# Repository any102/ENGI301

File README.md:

# ENGI301 <h>
Repository for ENGI 301 course work

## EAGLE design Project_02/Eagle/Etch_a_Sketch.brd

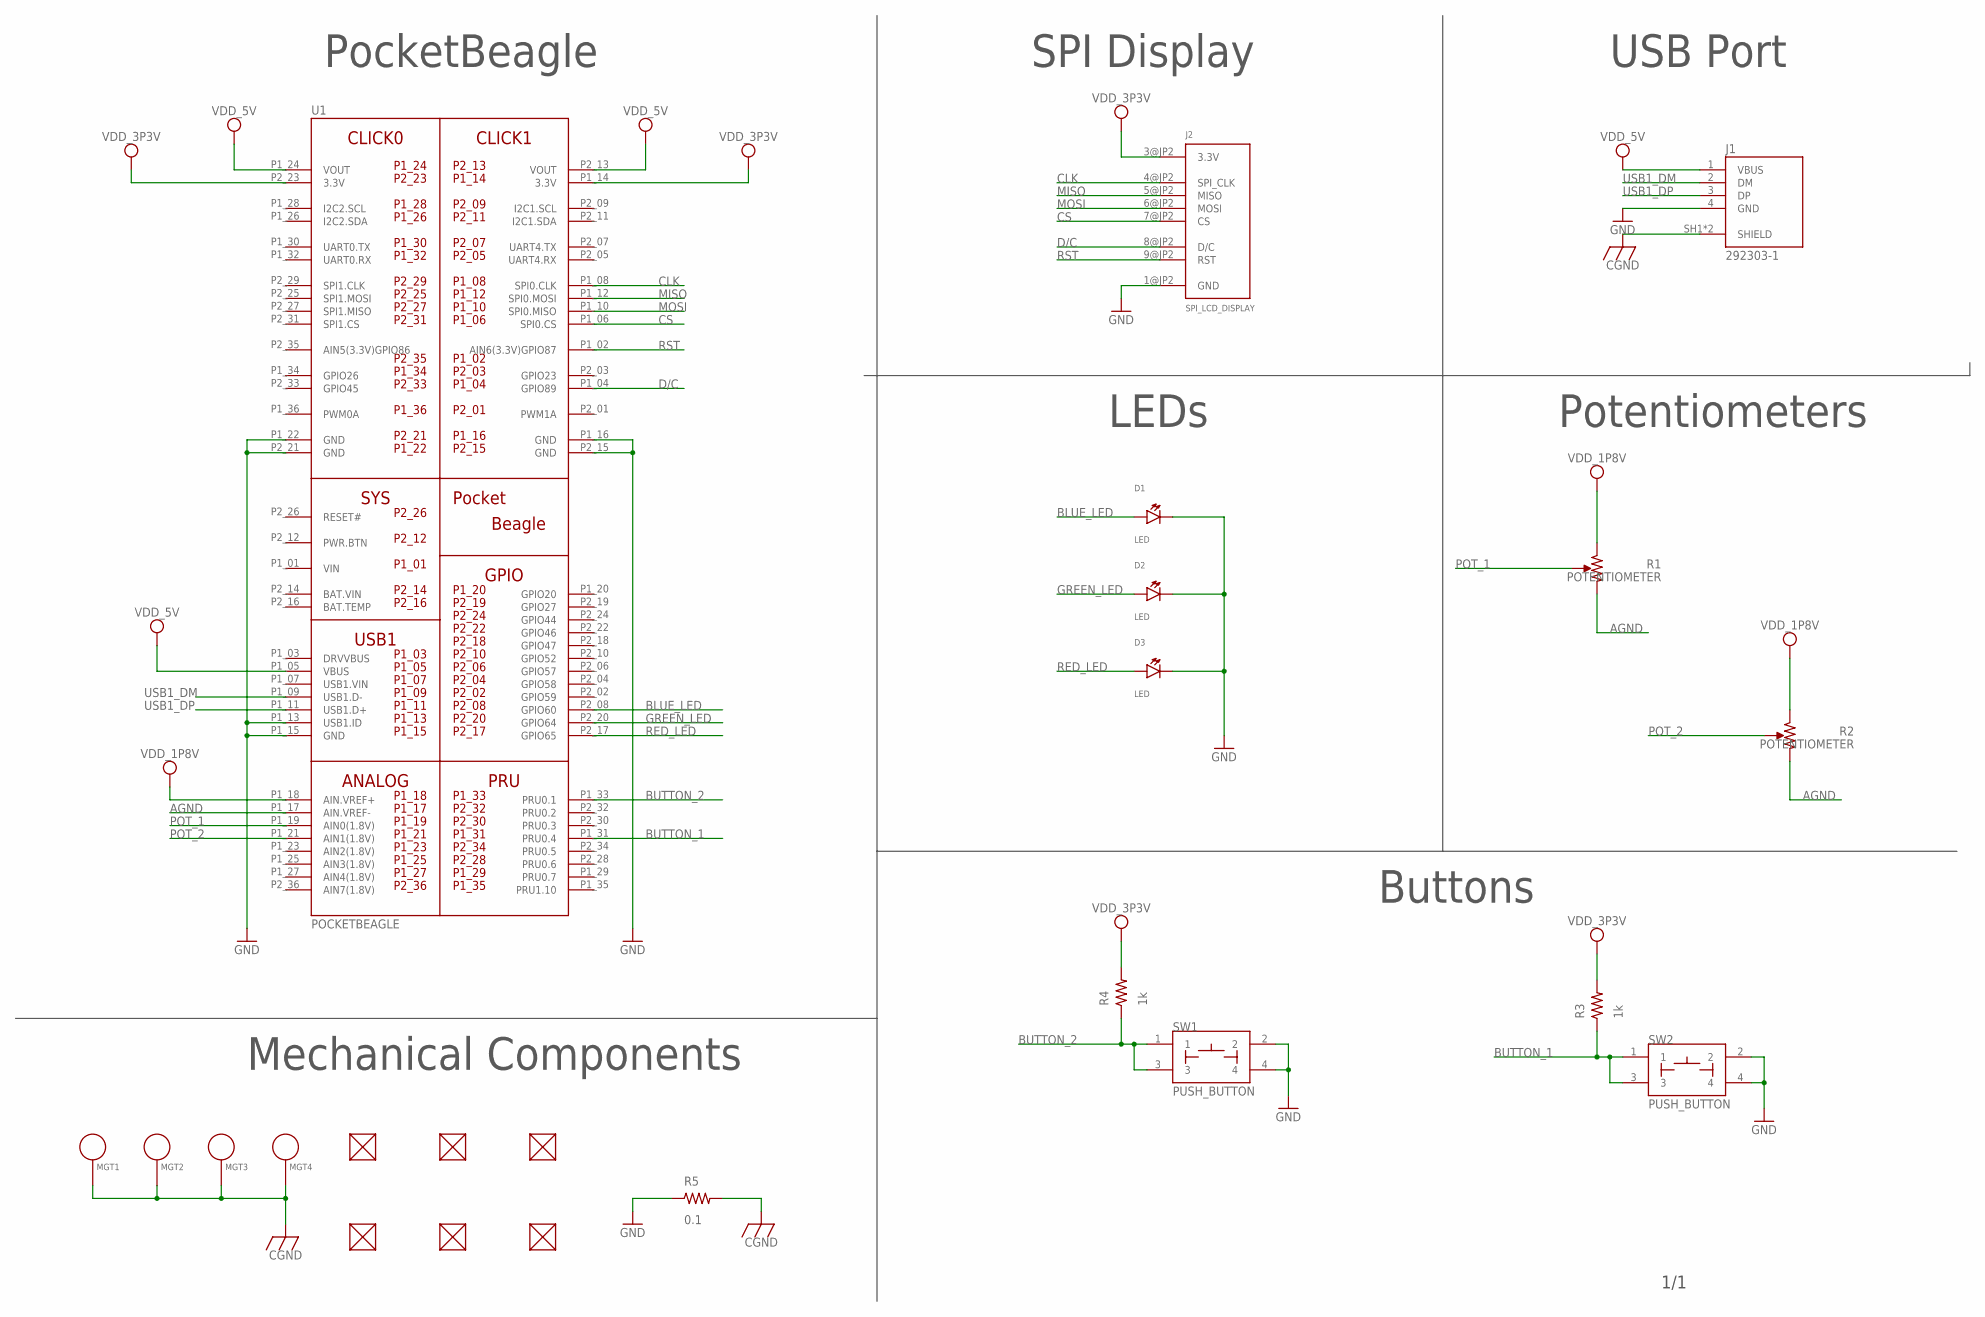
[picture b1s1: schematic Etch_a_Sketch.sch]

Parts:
D1, D2, D3: LED; EIA-STD
FUD1, FUD2, FUD3, FUD4, FUD5, FUD6: FIDUCIAL; FIDUCIAL_40MIL
J1: 292303-1; TE_292303-1
J2: SPI_LCD_DISPLAY
MGT1, MGT2, MGT3, MGT4: MOUNTING_HOLE
R1, R2: POTENTIOMETER; POT-PO90S
R3, R4: 1k; R0603
R5: 0.1; R0603
SW1, SW2: PUSH_BUTTON; BUTTON_12.5MM
U1: POCKETBEAGLE

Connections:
AGND: R1.CW, R2.CW, U1.P1_17 (AIN.VREF-)
BAT.VIN: U1.P2_14 (BAT.VIN)
BLUE_LED: D1.ANODE, U1.P2_08 (GPIO60)
BUTTON_1: R3.1, SW2.1, SW2.3, U1.P1_31 (PRU0.4)
BUTTON_2: R4.1, SW1.1, SW1.3, U1.P1_33 (PRU0.1)
CGND: J1.SH1 (SHIELD), J1.SH2 (SHIELD), MGT1.P$1, MGT2.P$1, MGT3.P$1, MGT4.P$1, R5.2
CLK: J2.4@JP2 (SPI_CLK), U1.P1_08 (SPI0.CLK)
CS: J2.7@JP2 (CS), U1.P1_06 (SPI0.CS)
D/C: J2.8@JP2 (D/C), U1.P1_04 (GPIO89)
GND: D1.CATHODE, D2.CATHODE, D3.CATHODE, J1.4 (GND), J2.1@JP2 (GND), R5.1, SW1.2, SW1.4, SW2.2, SW2.4, U1.P1_13 (USB1.ID), U1.P1_15 (GND), U1.P1_16 (GND), U1.P1_22 (GND), U1.P2_15 (GND), U1.P2_21 (GND)
GREEN_LED: D2.ANODE, U1.P2_20 (GPIO64)
MISO: J2.5@JP2 (MISO), U1.P1_12 (SPI0.MOSI)
MOSI: J2.6@JP2 (MOSI), U1.P1_10 (SPI0.MISO)
POT_1: R1.S, U1.P1_19 (AIN0(1.8V))
POT_2: R2.S, U1.P1_21 (AIN1(1.8V))
RED_LED: D3.ANODE, U1.P2_17 (GPIO65)
RST: J2.9@JP2 (RST), U1.P1_02 (AIN6(3.3V)GPIO87)
USB1_DM: J1.2 (DM), U1.P1_09 (USB1.D-)
USB1_DP: J1.3 (DP), U1.P1_11 (USB1.D+)
VDD_1P8V: R1.CCW, R2.CCW, U1.P1_18 (AIN.VREF+)
VDD_3P3V: J2.3@JP2 (3.3V), R3.2, R4.2, U1.P1_14 (3.3V), U1.P2_23 (3.3V)
VDD_5V: J1.1 (VBUS), U1.P1_05 (VBUS), U1.P1_24 (VOUT), U1.P2_13 (VOUT)
VIN: U1.P1_01 (VIN)

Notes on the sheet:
PocketBeagle
Mechanical Components
SPI Display
USB Port
LEDs
Potentiometers
Buttons
1/1

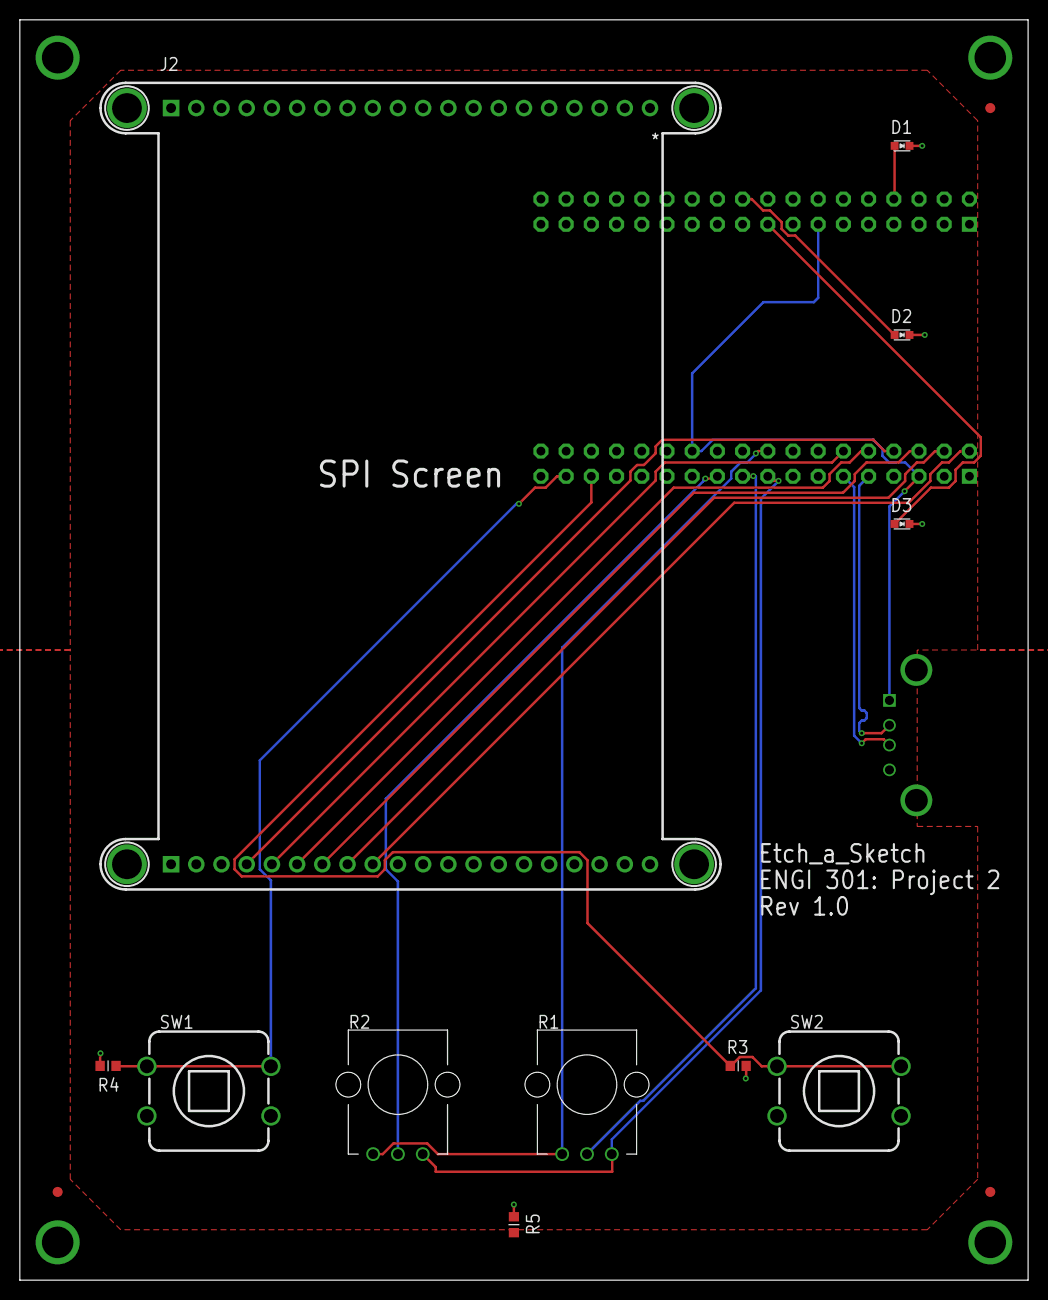
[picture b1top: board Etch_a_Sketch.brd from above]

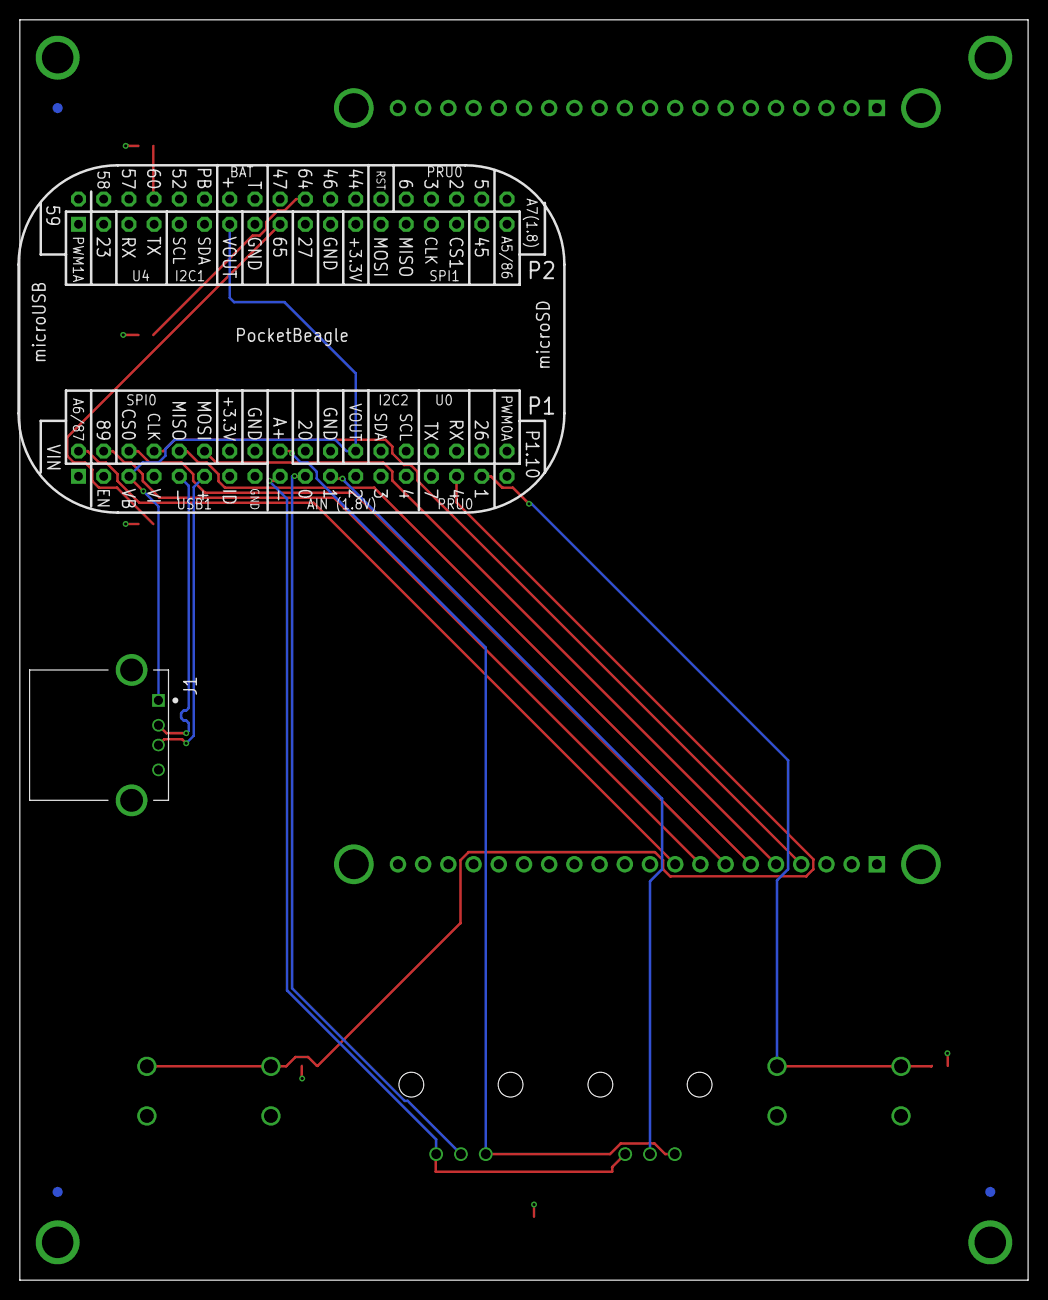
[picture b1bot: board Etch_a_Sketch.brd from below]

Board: 4 copper layers, 101.6 x 127.0 mm, 23 parts (5 on the bottom side), 21 nets.

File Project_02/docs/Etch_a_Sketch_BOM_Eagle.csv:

"Qty";"Value";"Device";"Package";"Parts";"Description";"AVAILABILITY";"CENTERLINE_PITCH";"COMMENT";"DESCRIPTION";"EU_ROHS_COMPLIANCE";"MF";"MP";"NUMBER_OF_POSITIONS";"PACKAGE";"PRICE";"PRODUCT_TYPE";"PURCHASE-URL";
"1";"0.1";"R_R0603";"R0603";"R5";"RESISTOR, American symbol";"";"";"";"";"";"";"";"";"";"";"";"";
"2";"1k";"R_R0603";"R0603";"R3, R4";"RESISTOR, American symbol";"";"";"";"";"";"";"";"";"";"";"";"";
"1";"292303-1";"292303-1";"TE_292303-1";"J1";"CONN USB RECEPT R/A TYPE A 4POS Check availability";"In Stock";"2 mm[.078 in]";"292303-1";" Conn";" Data";" USB";" Recept";" 2.0";" 4 Pos";" 1 Port";" Rt Angle";" A Ser";
"6";"FIDUCIAL";"FIDUCIAL";"FIDUCIAL_40MIL";"FUD1, FUD2, FUD3, FUD4, FUD5, FUD6";"";"";"";"";"";"";"";"";"";"";"";"";"";
"3";"LED";"LED";"EIA-STD";"D1, D2, D3";"EIA-STD LED, LTST-C191TBKT";"";"";"";"";"";"";"";"";"";"";"";"";
"4";"MOUNTING_HOLE";"MOUNTING_HOLE";"MOUNTING_HOLE";"MGT1, MGT2, MGT3, MGT4";"Chassis Mounting Hole w/GND connection ability";"";"";"";"";"";"";"";"";"";"";"";"";
"1";"POCKETBEAGLE";"POCKETBEAGLE";"POCKETBEAGLE";"U1";"";"";"";"";"";"";"";"";"";"";"";"";"";
"2";"POTENTIOMETER";"POTENTIOMETER";"POT-PO90S";"R1, R2";"Potentiometer - Examples:";"";"";"";"";"";"";"";"";"";"";"";"";
"2";"PUSH_BUTTON";"PUSH_BUTTON";"BUTTON_12.5MM";"SW1, SW2";"";"";"";"";"";"";"";"";"";"";"";"";"";
"1";"SPI_LCD_DISPLAY";"SPI_LCD_DISPLAY";"SPI_LCD_DISPLAY";"J2";"2.8" Adafruit SPI Display";"";"";"";"";"";"";"";"";"";"";"";"";

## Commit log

2022-09-27 adding simple calculator
2022-09-27 Adding LED blinker
2022-12-12 Create Project_1 folder
2022-12-12 Adding proposal powerpoint
2022-12-12 Adding display file
2022-12-12 Adding main python file
2022-12-12 Adding shell file
2022-12-14 Creating docs folder
